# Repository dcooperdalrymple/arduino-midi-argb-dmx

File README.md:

# Color Spray
> Convert Midi input to ARGB, RGBW, and DMX outputs with an Arduino.

## Hardware
This project is designed specifically for the [Adafruit Itsy Bitsy 32u4 - 5V 16MHz](https://learn.adafruit.com/introducting-itsy-bitsy-32u4/), but any other Arduino-compatible MCU with similar specifications should be usable with minor modifications. The PCB design will require modification to use a different development board.

For 5V/12V RGBW operation, you can choose between NPN or N-channel MOSFETs in a TO-220 package _(ie: IRF540N, IRLB8721, or TIP-120)_. The resistors before the gate may not be necessary if you use a MOSFET, but are necessary if you use an NPN transistor. If you are using 5V LEDs, you'll need to bridge JP1 and make sure not to also plug a 12V source into the barrel jack at the same time or you may fry the arduino and any devices plugged into the ARGB connectors. If you use 12V LEDs, make sure that JP1 is not connected and provide a separate 12V power source into the barrel jack that is center-positive.

An XLR connector is provided as an alternative to the ARGB pin header. This connector is non-standard and is intended for custom installations where long, secure cable runs are desired. Avoid mixing the DMX and ARGB connections, though I've attempted to make their pinouts very similar to avoid shorting.

## Configuration
The device's configuration is stored within the internal EEPROM memory of the Atmel 32u4. If the appropriate configuration settings aren't already installed, the device will reformat the EEPROM to it's default settings. Midi SysEx messages are used in order to read and write new configuration settings.

A python-based configurator GUI program is provided to help read, backup, and write device configuration to the Color Spray. The program can be run after installing all [dependencies](configurator/manual.md#dependencies) by running `python configurator/configurator.py` from the root directory of the repository. More information is provided in the [manual](configurator/manual.md).

<p float="left">

</p>

## MIDI Implementation

### Configuration

> Depending on how the software is compiled and uploaded to the Arduino, you can use hardware UART Midi or USB Midi to control this device. The Rev1 PCB is configured with a DIN-5 Midi input only. Future revisions may include Midi output.

Change the `USB_MIDI` definition to enable USB Midi input support. The `MIDI_THRU` definition will enable Midi Thru support via hardware UART and USB if it is enabled.

By default, the `MIDI_CHANNEL` definition is set to Omni mode. This will accept all compatible incoming messages on any channel. Change the value of this definition to a number between 1-16 to assign this device to a particular Midi channel.

### Midi Thru

Some software-based Midi Thru functionality is included, but not all message types are supported. It is recommended that you use a hardware Midi Thru device in conjuction if you intend to use multiple devices on the same output.

### Program Change

> More program modes are planned for the future.

| Program | Description   |
| ------- | ------------- |
| 0       | Off           |
| 1-15    | Load Preset # |
| 16      | Solid RGB     |
| 17      | Solid HSV     |
| 18      | Palette Cycle |
| 19      | Chase RGB     |
| 20      | Chase HSV     |

### Control Change

Control change messages are generally allocated to different General Purpose Controller functions and are separated for each program mode.

| Control | Function   | Value (0-127, scaled)    | Program               |
| ------- | ---------- | ------------------------ | --------------------- |
| 12      | Palette    | _See Available Palettes_ | Palette Cycle         |
| 13      | Speed      | 0-4                      | Palette Cycle & Chase |
| 16      | Red        | 0-254                    | Solid RGB & Chase RGB |
| 17      | Green      | 0-254                    | Solid RGB & Chase RGB |
| 18      | Blue       | 0-254                    | Solid RGB & Chase RGB |
| 80      | Hue        | 0-254                    | Solid HSV & Chase HSV |
| 81      | Saturation | 0-254                    | Solid HSV & Chase HSV |
| 82      | Value      | 0-254                    | Solid HSV & Chase HSV |
| 83      | Count      | 1-8                      | Chase RGB & Chase HSV |

#### Palettes

There are 8 palettes available all contributed by the _FastLED_ library. Custom palettes can be added relatively easily prior to compilation. See the [FastLED wiki](https://github.com/FastLED/FastLED/wiki/Gradient-color-palettes) for more details.

| Index | Midi CC Value | Palette        |
| ----- | ------------- | -------------- |
| 0     | 0-15          | Cloud          |
| 1     | 16-31         | Lava           |
| 2     | 32-47         | Ocean          |
| 3     | 48-63         | Forest         |
| 4     | 64-79         | Rainbow        |
| 5     | 80-95         | Rainbow Stripe |
| 6     | 96-111        | Party          |
| 7     | 112-127       | Heat           |

## DAW Plugins

> The only plugin provided for improved control and synchronization of this device is written for REAPER. The specifications are all provided for extending support to other platforms, but that is not planned currently.

### REAPER (JSFX)

Use the provided sliders to configure this device or enable trim automation on each setting to synchronize your lighting to your song.

Copy and paste `plugins/color-spray-jsfx` into your REAPER JSFX install directory (ie: .../REAPER/Effects). Add the plugin to a track in your project; it will be named _Color Spray_.

## Software Dependencies
* [MIDI](https://github.com/FortySevenEffects/arduino_midi_library/)
* [Arduino USB-MIDI Transport](https://github.com/lathoub/Arduino-USBMIDI)
* [FastLED](https://fastled.io/)
* [DmxSimple](https://github.com/PaulStoffregen/DmxSimple)
* [digitalWriteFast](https://github.com/NicksonYap/digitalWriteFast)

---

[OSHW] US002117 | Certified open source hardware | oshwa.org/cert.

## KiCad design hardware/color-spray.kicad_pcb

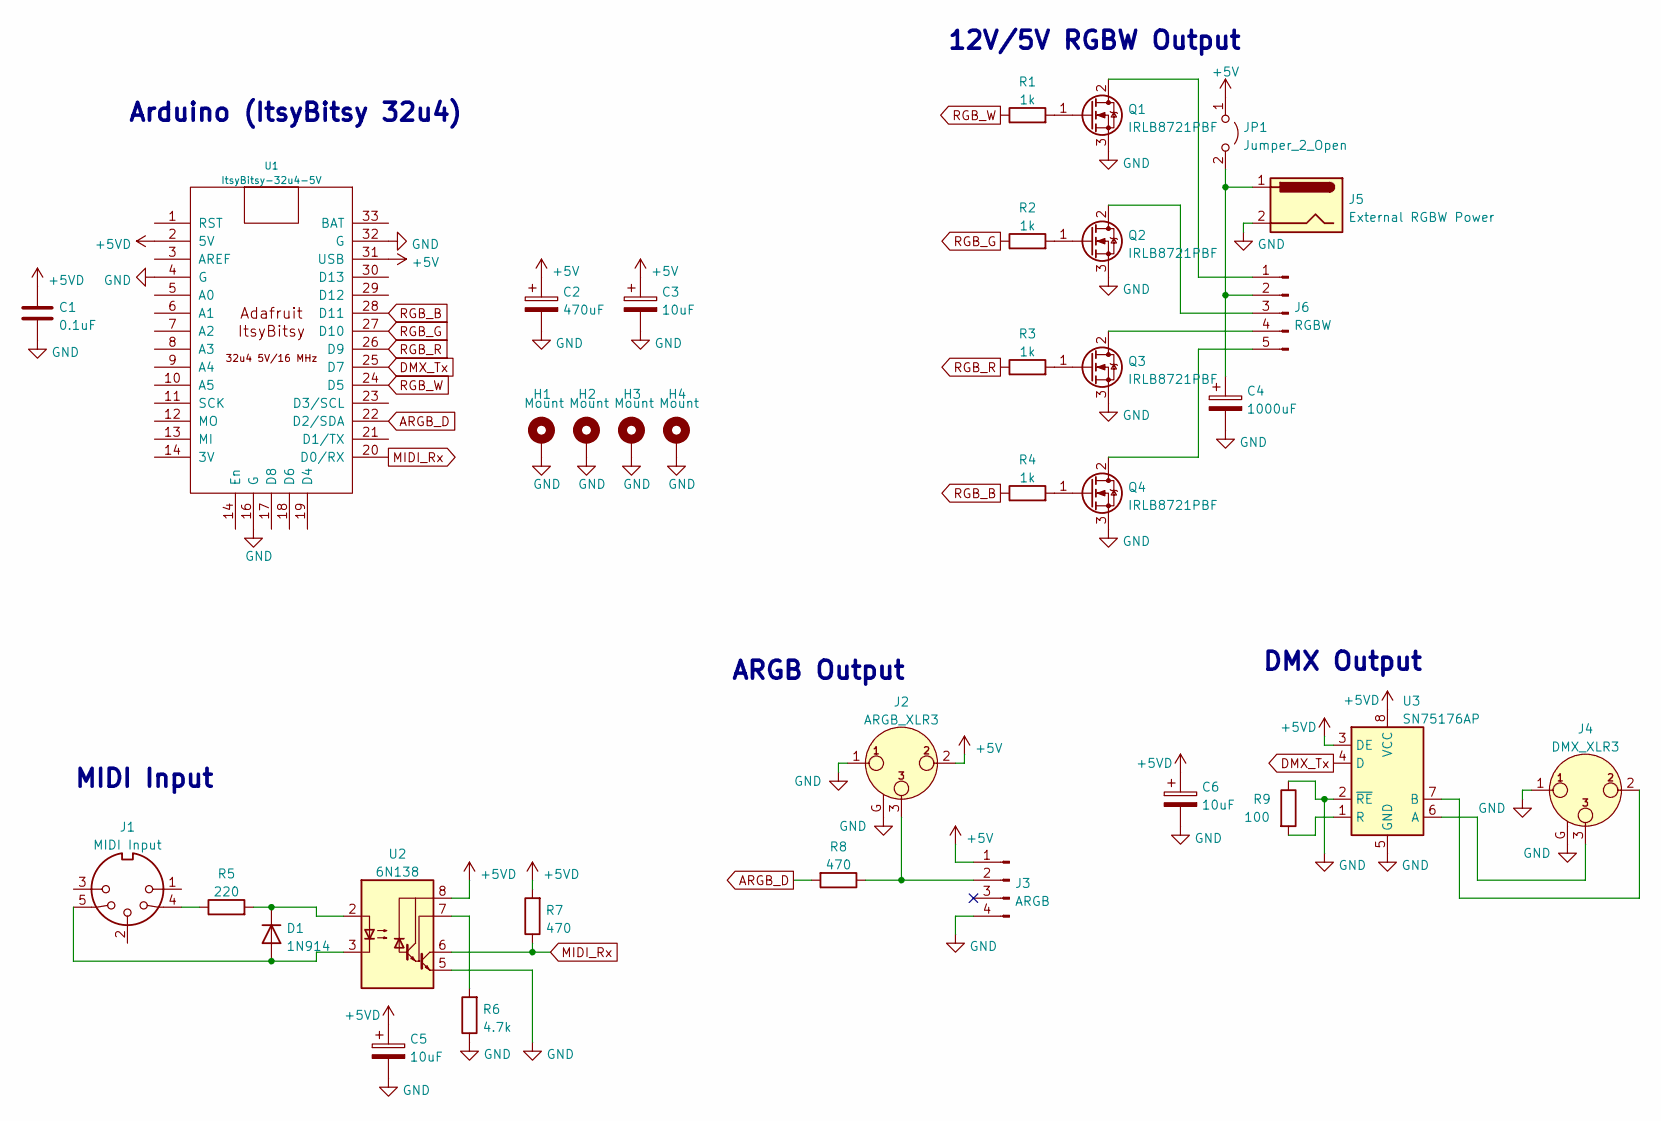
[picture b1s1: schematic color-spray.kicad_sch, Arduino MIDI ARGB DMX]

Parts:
C1: 0.1uF; C_Rect_L4.0mm_W2.5mm_P2.50mm
C2: 470uF; CP_Axial_L20.0mm_D10.0mm_P26.00mm_Horizontal
C3, C5, C6: 10uF; CP_Radial_D5.0mm_P2.50mm
C4: 1000uF; CP_Axial_L20.0mm_D10.0mm_P26.00mm_Horizontal
D1: 1N914; D_DO-35_SOD27_P7.62mm_Horizontal
H1, H2, H3, H4: Mount; MountingHole_3.2mm_M3_Pad
J1: MIDI Input; din-5
J2: ARGB_XLR3; Jack_XLR_Neutrik_NC3FAAH2_Horizontal
J3: ARGB; PinHeader_1x04_P2.54mm_Horizontal
J4: DMX_XLR3; Jack_XLR_Neutrik_NC3FAAH2_Horizontal
J5: External RGBW Power; BarrelJack_Horizontal
J6: RGBW; PinHeader_1x05_P2.54mm_Horizontal
JP1: Jumper_2_Open; PinHeader_1x02_P2.54mm_Vertical
Q1, Q2, Q3, Q4: IRLB8721PBF; TO-220-3_Vertical
R1, R2, R3, R4: 1k; R_Axial_DIN0207_L6.3mm_D2.5mm_P7.62mm_Horizontal
R5: 220; R_Axial_DIN0207_L6.3mm_D2.5mm_P7.62mm_Horizontal
R6: 4.7k; R_Axial_DIN0207_L6.3mm_D2.5mm_P7.62mm_Horizontal
R7, R8: 470; R_Axial_DIN0207_L6.3mm_D2.5mm_P7.62mm_Horizontal
R9: 100; R_Axial_DIN0207_L6.3mm_D2.5mm_P7.62mm_Horizontal
U1: ItsyBitsy-32u4-5V; ItsyBitsy_32u4
U2: 6N138; DIP-8_W7.62mm_Socket_LongPads
U3: SN75176AP; DIP-8_W7.62mm_Socket_LongPads

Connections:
+5V: C2.1, C3.1, J2.2, J3.1, JP1.1 (A), U1.31 (USB)
+5VD: C1.1, C5.1, C6.1, R7.2, U1.2 (5V), U2.8 (VCC), U3.3 (DE), U3.8 (VCC)
ARGB_D: R8.2, U1.22 (D2/SDA)
DMX_Tx: U1.25 (D7), U3.4 (D)
GND: C1.2, C2.2, C3.2, C4.2, C5.2, C6.2, H1.1, H2.1, H3.1, H4.1, J2.1, J2.G, J3.4, J4.1, J4.G, J5.2, Q1.3 (S), Q2.3 (S), Q3.3 (S), Q4.3 (S), R6.1, R9.1, U1.4 (G), U1.16 (G), U1.32 (G), U2.5 (GND), U3.2 (~RE), U3.5 (GND)
MIDI_Rx: R7.1, U1.20 (D0/RX), U2.6 (VO2)
unnamed: C4.1, J5.1, J6.2, JP1.2 (B)
unnamed: J1.4, R5.1
unnamed: D1.2 (A), J1.5, U2.3 (C2)
unnamed: J2.3, J3.2, R8.1
unnamed: J4.2, U3.7 (B)
unnamed: J4.3, U3.6 (A)
unnamed: J6.3, Q2.2 (D)
unnamed: J6.4, Q3.2 (D)
unnamed: J6.5, Q4.2 (D)
unnamed: J6.1, Q1.2 (D)
unnamed: Q1.1 (G), R1.2
unnamed: Q2.1 (G), R2.2
unnamed: Q3.1 (G), R3.2
unnamed: Q4.1 (G), R4.2
unnamed: D1.1 (K), R5.2, U2.2 (C1)
unnamed: R6.2, U2.7 (VO1)
unnamed: R9.2, U3.1 (R)
RGB_B: R4.1, U1.28 (D11)
RGB_G: R2.1, U1.27 (D10)
RGB_R: R3.1, U1.26 (D9)
RGB_W: R1.1, U1.24 (D5)

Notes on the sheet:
MIDI Input
Arduino (ItsyBitsy 32u4)
ARGB Output
12V/5V RGBW Output
DMX Output

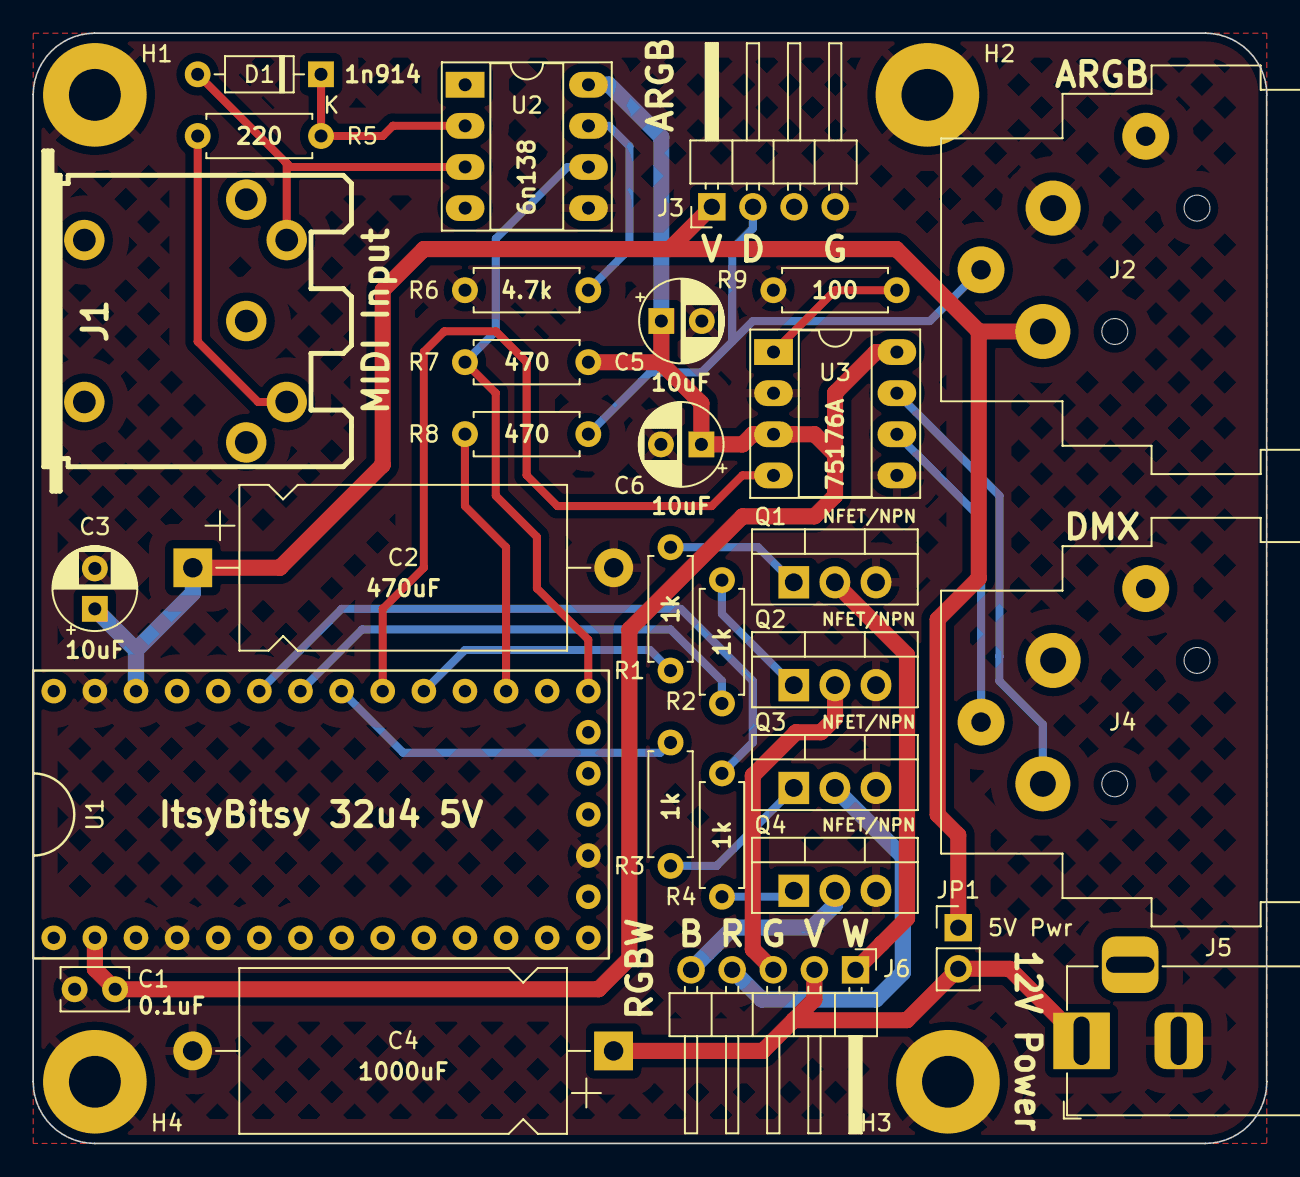
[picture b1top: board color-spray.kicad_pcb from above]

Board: 2 copper layers, 76.2 x 68.6 mm, 34 parts (0 on the bottom side), 27 nets.

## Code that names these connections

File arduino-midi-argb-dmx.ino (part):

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#define DMX_ORDER       GBR
CRGB *dmxLights;

#define RGB_R           9
#define RGB_G           10
#define RGB_B           11
#define RGB_W           5

#define COLOR_UPDATE    10
#define PALETTE_UPDATE  1
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
    FastLED.setBrightness(settings.getBrightness());

    pinMode(RGB_R, OUTPUT);
    analogWrite(RGB_R, 0);
    pinMode(RGB_G, OUTPUT);
    analogWrite(RGB_G, 0);
    pinMode(RGB_B, OUTPUT);
    analogWrite(RGB_B, 0);
    pinMode(RGB_W, OUTPUT);
    analogWrite(RGB_W, 0);

    if (settings.getPreset() > 0) {
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
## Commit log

2022-05-07 First prototype build of hardware & software.
2022-05-07 Revision 1 of PCB. Provided support for 5V or 12V analog LED strips.
2022-05-09 Added USB MIDI and Serial In to USB Out thru support.
2022-05-09 Added RGBW support. Simple algorithm that might need improvement.
2022-05-25 Led Trigger, Usb Midi/Debug option, Hardware Thru, Palette Changes refinement, Color Off mode, Program Change mode, CC codes, and more.
2022-05-25 Reaper JSFX control plugin.
2022-05-25 Hardware BOM
2022-05-25 Added palette scaling.
2022-05-25 Updated readme and images.
2022-05-27 FreeCAD Enclosure
2022-05-27 DMX TX pin fix.
2022-05-27 EEPROM settings, DmxSimple through FastLED, dynamically allocated lights, dynamic ARGB type.
2022-05-27 USB Midi input support and improved Midi Thru.
2022-05-31 Switched from MIDIUSB to Arduino USB-MIDI Transport to consolidate midi logic.
2022-05-31 Added preset support.
2022-05-31 Sysex EEPROM writing for settings and presets.
2022-06-02 Configurator tool.
2022-06-02 Usb Midi improvements, sysex implementation, default preset, and NoteOn preset triggering.
2022-06-02 Reorganization and renaming.
2022-06-03 Progress bar and text.
2022-06-03 Consolidated menu.
2022-06-03 Updated enclosure labels.
2022-06-04 Sysex response data size allocation optimization.
2022-06-04 DMX RGB order fix.
2022-06-04 Dynamic configuration with new sysex reset command.
2022-06-04 Custom DMX controller. Bump in settings version to 2.
2022-06-04 Separate color indexing rates for ARGB and DMX.
2022-06-04 Added OSHWA certification mark to PCB and README.
2022-06-05 Configurator program manual.
2022-06-06 About and manual dialogs.
2022-06-06 Added configurator screenshots.
2022-06-07 Added ChaseRGB/ChaseHSV color modes. New count preset parameter (CC #83). Settings version pushed to 3.
2022-06-07 Program Change messages now affect both Preset and Color Mode.
2022-06-09 Performance optimization. ARGB type is compile-time; removed settings option. Pushed settings version to 4.
2022-08-11 Rewrite of controllers (ARGB, DMX, RGBW) to dynamically generate colors rather than use bulky arrays. Merge of some FastLED depedencies for color calculations. Added digitalWriteFast dependency. Need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
2024-01-04 Fixed OSHWA ID

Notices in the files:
arduino-midi-argb-dmx.ino:
License: GNU GPL v3.0
